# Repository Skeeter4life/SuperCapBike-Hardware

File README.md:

# This repository contains all the hardware needed for my supercapacitor bike.

## Main Features

  A 2 x ((500F @ 2.7V) x 6)  super-capacitor bank-based accumulator:
  
      1. Ability to provide high amounts of current instantaneously.
      
        This is well suited for my application where immediate throttle response is required. 
        The instant delivery of torque allows for aggressive accelerations when 
        changing from a low throttle position to full throttle.  

      2. Much more durable than a traditional battery.
        
        The super-capacitors can withstand many more full charge and discharge cycles
        without degradation. As such, they will undergo many charging cycles through 
        sources such as regenerative braking. Long service life is a priority.
      
      3. Quick charge times.

        Since super-capacitors have significantly less charge density than a battery, 
        it results in faster charging times. The primary intent is to only discharge 
        the super-capacitors to assist in climbing a hill.

  Series-Parallel Switching:

    This allows for a much more dynamic control over the power delivery from the super-capacitors. 
    To maximize runtime, the capacitors can be placed in parallel. 
    When the capacitors are getting low, or a large amount of power is required, 
    they can be switched into series. 

  More specific details can be found [here](https://www.desmos.com/calculator/0xlkaikos0).
    
## Current Components List

Ceramic Capacitors: 
- 0.1uF x 7 [^1], 
- 0.33uF x 2 [^2],
- 1uF x 3 [^3]

Electrolytic capacitors: 
- 10uF x 4 [^4]
  
Diodes:
- 1N4148 x 3 [^5], 
- 1N5819 x 5 [^6]

LEDs: 
- 5.0mm THT x2 [^7]

Fuse: 
- 0225002.MXP x1 [^8], 
- F4658-ND x 1 [^9]

Sockets & Pins: 
- 1x01 1.00mm Vertical Male Pin x 5 [^10], 
- 8 Dip 7.62mm Socket x 5 [^11],
- 16 Dip 7.62mm Socket x 1 [^12], 
- 28 Dip 7.62mm Socket x2 [^13] 

Barrel Jack: 
- PJ_002AH x 1 [^14]

Relays: 
- AWHSH105D00G x 2 [^15]

MOSFETS:
- IRFZ44N x 7 [^16], 
- GT065P06T x 1 [^17]

Resistors: 
- 0Ω, 10Ω, 220Ω, 10kΩ, 22kΩ Resistor Kit: [^18] (Not included in total price!)

Terminals: 
- 1988804 x 1 [^19], 
- 1988817 x 2 [^20], 
- 1190363 x2  [^21], 
- 1988862 x 3 [^22]

Microprocessors: 
- ATMEGA328P x 1 [^23]

Crystal Oscillator: 
- MXO45HST-3C-16M000000 x 1 [^24]

GPIO Expander: 
- MCP23017 x 1 [^25]

Button: 
- TS02-66-50-BK-160-LCR-D x 1 [^26]

MOSFET Gate Driver: 
- UCC37324P x 1 [^27] *OPTIONAL*

Darlington Transistors Array: 
- ULN2003 x 1 [^28]

Digital Potentiometers: 
- MCP4151 x 1 [^29]

Half Bridge Drivers: 
- IR2104 x 3 [^30]

Linear Regulators: 
- L7805 x1 [^31], 
- L78L33ACZ x1 [^32] (Considering upgrading to one that can output more current, I have not decided on display yet, but I had it)

Hall Effect Sensors: 
- TMAG5213AGQLPG x 3 [^33]

Switches: 
- 2057-SW-R-K1-A-ND x 1 [^34] 

Subtotal: **$ 98.21 CAD**

## Schematic and PCB

### Schematic:  

  To reduce image congestion, please clone the repository and access the schematic on Kicad V8+.

### PCB:

<div align="center">

</div>

## FAQ

  -Q: Why are you using only through-hole components?
  
  -A: Since some of these components are new to me, I wanted to be able to quickly set up and re-arrange components on a breadboard so I can fiddle and experiment with them.

  -Q: Why did you choose to design your PCB only with 2 layers?
  
  -A: As the current PCB is only a prototype, I did my best to mitigate EMI, however, I was not too overly concerned with it. I am considering isolating analog and digital ground. My main focus is to test my circuit design on a 2-layer 1oz copper pour PCB and see if any issues need addressing before proceeding to designing a more expensive 2oz copper 4-layer PCB.

  -Q: Why are you using a dedicated MOSFET driver IC to control Q8?
  
  -A: Admittedly, this component is completely optional and absolutely can be replaced with a simple current limiting resistor. Naturally, this does affect the switching speed of the transistor, and I want to maximize performance. I have the IC in hand, and the favourable transient response led me to implement it into my circuit.

  -Q: Why the relays?
  
  -A: I was able to simulate and build a circuit that switches two capacitors in series or parallel with only MOSFETS, however the performance when V_GS < ~4V was inadequate. Additionally, diodes were required to prevent reverse currents from connecting C2- to GND. As such, relays had significantly greater performance when switching the super-capacitors into parallel. I still kept Q7 and Q8 to switch the capacitors into series as a tribute to what I have learned from my experience with MOSFETs.

  -Q: Why did you choose the IRFZ44N?
  
  -A: The IRFZ44N is a widely used, affordable n-type MOSFET, as of which I have many on hand. I am well within the limitations of the drain current I_D, and drain source voltage V_DS. It has a favourable characteristic of only needing a V_GS of ~5.5V to supply 10A at a V_DS of ~ 0.3V. All transients were more than acceptable with the chosen MOSFET drivers for my         application.  

  -Q: Why did you choose the GT065P06T?
  
  -A: I chose the GT065P06T primarily due to its outstanding R_DS of < 11mΩ at V_GS -4.5V for a p-type MOSFET and low gate charge. When the capacitors are in series, I want to minimize the power dissipated through that MOSFET without using PWM. 

## What I am Working on Now

I am currently installing the Hall effect sensors into the motor. The previous sensors were faulty and only outputted an average analog voltage of +3mV. An attempt was made to filter the signal from significant noise with the use of Schmitt triggers, however, this added significantly more complexity and cost. A replacement of the sensors was deemed to be the optimal solution.

## Personal Note

Somehow I managed to get sick twice throughout the last two months! I am doing my best to balance schoolwork and look over my design. I hope to have the PCB ordered by the end of October.

PCB ORDERED! :O

## Sources

[^1]: https://www.digikey.ca/en/products/detail/kemet/C322C104M5U5TA/818107
[^2]: https://www.digikey.ca/en/products/detail/kemet/C330C334M5R5TA/6562403
[^3]: https://www.digikey.ca/en/products/detail/kemet/C330C105K5R5TA7301/3726162
[^4]: https://www.digikey.ca/en/products/detail/cornell-dubilier-knowles/106CKE400M/5410625
[^5]: https://www.digikey.ca/en/products/detail/onsemi/1N4148/458603
[^6]: https://www.digikey.ca/en/products/detail/stmicroelectronics/1N5819/1037326
[^7]: https://www.digikey.ca/en/products/detail/marktech-optoelectronics/MT4118-HR-A/4214622
[^8]: https://www.digikey.ca/en/products/detail/littelfuse-inc/02540101Z/553102
[^9]: https://www.digikey.ca/en/products/detail/littelfuse-inc/0225002-MXP/777781
[^10]: https://www.digikey.ca/en/products/detail/samtec-inc/TS-101-T-A/1105493
[^11]: https://www.digikey.ca/en/products/detail/te-connectivity-amp-connectors/1-2199298-2/5022039
[^12]: https://www.digikey.ca/en/products/detail/on-shore-technology-inc/ED16DT/4147596
[^13]: https://www.digikey.ca/en/products/detail/adam-tech/ICS-328-T/9832859
[^14]: https://www.digikey.ca/en/products/detail/same-sky/PJ-002AH/408446
[^15]: https://www.digikey.ca/en/products/detail/amphenol-anytek/AWHSH105D00G/16721986
[^16]: https://www.digikey.ca/en/products/detail/umw/IRFZ44N/24889964
[^17]: https://www.digikey.ca/en/products/detail/goford-semiconductor/GT065P06T/18088004
[^18]: https://www.digikey.ca/en/products/detail/sparkfun-electronics/COM-10969/14671649
[^19]: https://www.digikey.ca/en/products/detail/phoenix-contact/1988804/950892
[^20]: https://www.digikey.ca/en/products/detail/phoenix-contact/1988817/950893
[^21]: https://www.digikey.ca/en/products/detail/phoenix-contact/1190363/14680902
[^22]: https://www.digikey.ca/en/products/detail/phoenix-contact/1988862/950898
[^23]: https://www.digikey.ca/en/products/detail/microchip-technology/ATMEGA328P-PN/2357094
[^24]: https://www.digikey.ca/en/products/detail/cts-frequency-controls/MXO45HST-3C-16M000000/1801910
[^25]: https://www.digikey.ca/en/products/detail/microchip-technology/MCP23017-E-SP/894272
[^26]: https://www.digikey.ca/en/products/detail/same-sky-formerly-cui-devices/TS02-66-50-BK-160-LCR-D/15634352?s=N4IgTCBcDaICoGUAMYC0A2dqCsTUCEBpVARnTwBkBhAJVQBEACEAXQF8g
[^27]: https://www.digikey.ca/en/products/detail/texas-instruments/UCC37324P/571464
[^28]: https://www.digikey.ca/en/products/detail/stmicroelectronics/ULN2003A/599603
[^29]: https://www.digikey.ca/en/products/detail/microchip-technology/MCP4151-103E-P/1874217
[^30]: https://www.digikey.ca/en/products/detail/infineon-technologies/IR2104PBF/812198
[^31]: https://www.digikey.ca/en/products/detail/stmicroelectronics/L7805CV/585964
[^32]: https://www.digikey.ca/en/products/detail/stmicroelectronics/L78L33ACZ/1038304
[^33]: https://www.digikey.ca/en/products/detail/texas-instruments/TMAG5213AGQLPG/22531584
[^34]: https://www.digikey.ca/en/products/detail/adam-tech/SW-R-K1-A/15284469

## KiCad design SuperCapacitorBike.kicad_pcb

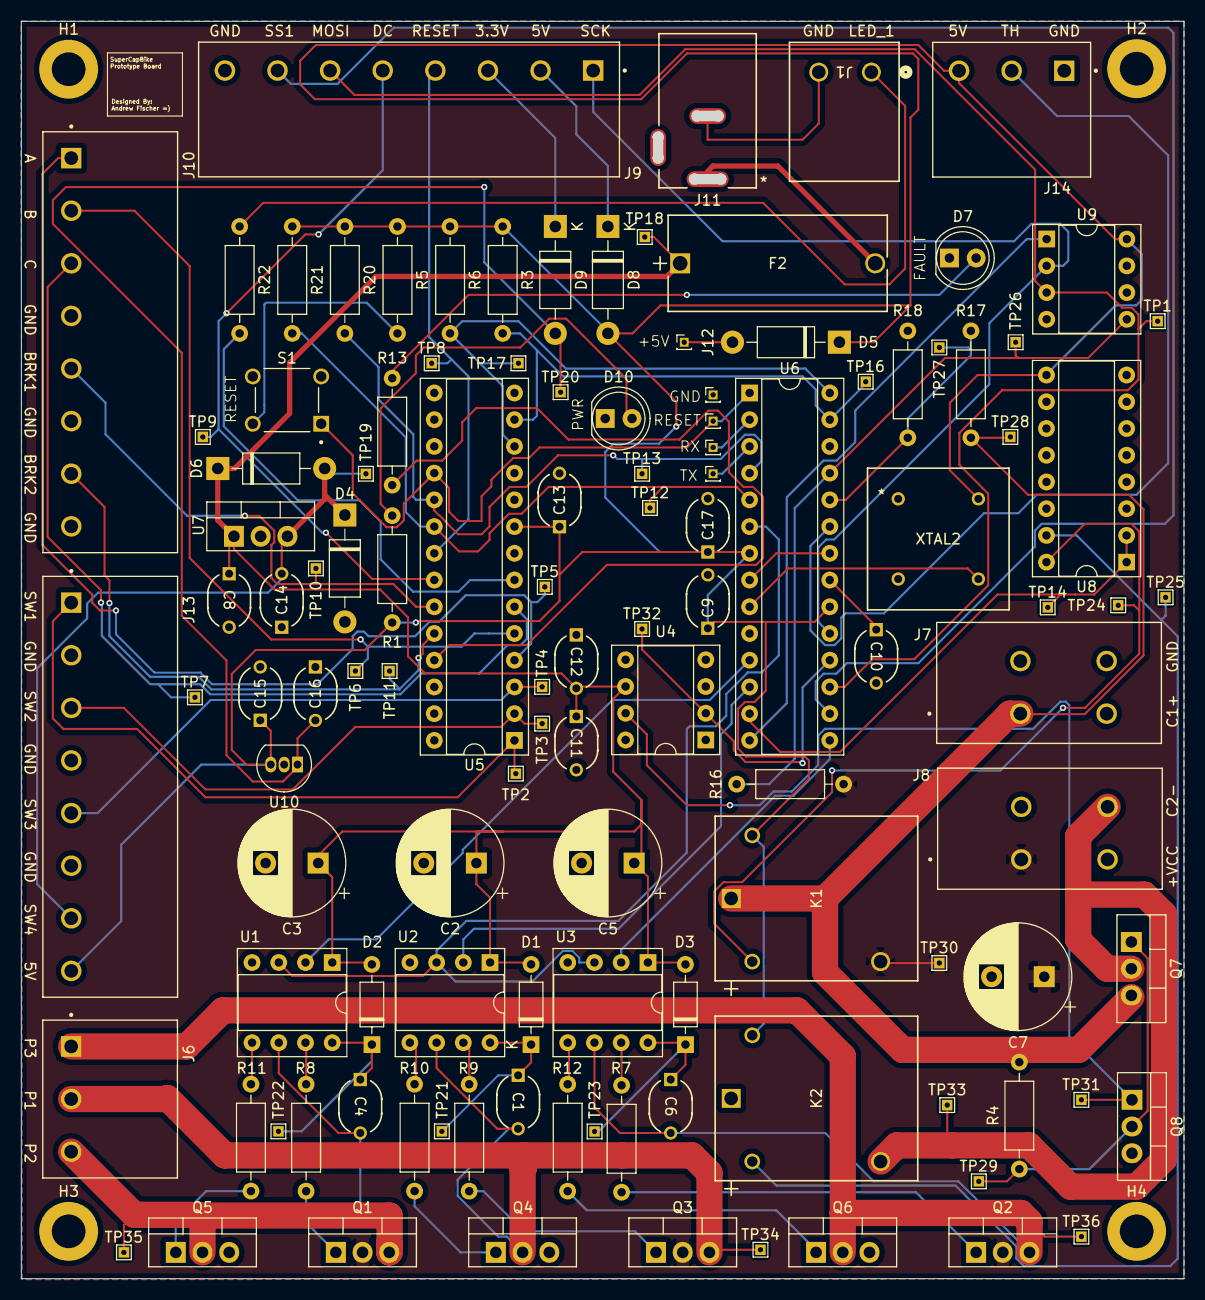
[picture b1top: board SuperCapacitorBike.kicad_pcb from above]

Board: 2 copper layers, 110.5 x 119.5 mm, 121 parts (0 on the bottom side), 71 nets.

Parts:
C1, C4, C6: 1uF; Ceramic_Cap_5.08mm_Spacing
C2, C3, C5, C7: 10uF; CP_Radial_D10.0mm_P5.00mm
C8, C15: 0.33uF; Ceramic_Cap_5.08mm_Spacing
C9, C10, C11, C13, C14, C16, C17: 0.1uF; Ceramic_Cap_5.08mm_Spacing
C12: 1.0uF; Ceramic_Cap_5.08mm_Spacing
D1, D2, D3: 1N4148; D_DO-35_SOD27_P7.62mm_Horizontal
D4, D5, D6, D8, D9: 1N5819; D_DO-41_SOD81_P10.16mm_Horizontal
D7: FAULT_LED; LED_D5.0mm
D10: PWR_LED; LED_D5.0mm
F2: 0225002.MXP; FUSE_254_PC_LTF
H1, H2, H3, H4: MountingHole_Pad; MountingHole_3.2mm_M3_DIN965_Pad
J1: 1988804; CONN_1988804
J2: GND; PinHeader_1x01_P1.00mm_Vertical
J3: RX; PinHeader_1x01_P1.00mm_Vertical
J4: TX; PinHeader_1x01_P1.00mm_Vertical
J5: RESET; PinHeader_1x01_P1.00mm_Vertical
J6, J14: 1988817; PHOENIX_1988817
J7, J8: 1190363; PHOENIX_1190363
J9, J10, J13: 1988862; PHOENIX_1988862
J11: Barrel_Jack_Switch; PJ-002AH_CUD
J12: +5V; PinHeader_1x01_P1.00mm_Vertical
K1, K2: AWHSH105D00G; AWHSH1xxD00G_AMP
Q1, Q2, Q3, Q4, Q5, Q6, Q8: IRFZ44N; TO-220-3_Vertical
Q7: GT065P06T; TO-220-3_Vertical
R1, R13, R22: 220Ω; R_Axial_DIN0207_L6.3mm_D2.5mm_P10.16mm_Horizontal
R3, R4, R5, R6, R20, R21: 10kΩ; R_Axial_DIN0207_L6.3mm_D2.5mm_P10.16mm_Horizontal
R7, R8, R9, R10, R11, R12: 47Ω; R_Axial_DIN0207_L6.3mm_D2.5mm_P10.16mm_Horizontal
R16: 20kΩ; R_Axial_DIN0207_L6.3mm_D2.5mm_P10.16mm_Horizontal
R17: 55kΩ; R_Axial_DIN0207_L6.3mm_D2.5mm_P10.16mm_Horizontal
R18: 25kΩ; R_Axial_DIN0207_L6.3mm_D2.5mm_P10.16mm_Horizontal
S1: TS02-66-50-BK-160-LCR-D; SW_TS02-66-50-BK-160-LCR-D
TP1, TP2, TP3, TP4, TP5, TP6, TP7, TP8, TP9, TP10, TP11, TP12, TP13, TP14, TP16, TP17, TP18, TP19, TP20, TP21, TP22, TP23, TP24, TP25, TP26, TP27, TP28, TP29, TP30, TP31, TP32, TP33, TP34, TP35, TP36: TestPoint; TestPoint_THTPad_1.0x1.0mm_Drill0.5mm
U1, U2, U3: IR2104; DIP-8_W7.62mm_Socket
U4: UCC37324P; DIP-8_W7.62mm_Socket
U5: MCP23017_SP; DIP-28_W7.62mm_Socket
U6: ATmega328-P; DIP-28_W7.62mm_Socket
U7: L7805; TO-220-3_Vertical
U8: ULN2003; DIP-16_W7.62mm_Socket
U9: MCP4151-xxxx-P; DIP-8_W7.62mm_Socket
U10: L78L33_TO92; TO-92_Inline
XTAL2: MXO45HST-3C-16M000000

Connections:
+3.3V: C16.2, D9.2 (A), TP20.1, U10.1 (VO)
+5V: C9.1, C13.1, C15.1, C17.1, D5.1 (K), D8.2 (A), J13.8, J14.3, K1.5, K2.5, R1.1, R3.1, R5.1, R6.1, R20.1, R21.1, U5.9 (VDD), U6.7 (VCC), U6.20 (AVCC), U8.9 (COM), U9.8 (V_{DD}), U10.3 (VI), XTAL2.8 (VCC)
+12V: C2.1, C3.1, C5.1, C8.1, C11.1, C12.2, D1.2 (A), D2.2 (A), D3.2 (A), D6.1 (K), F2.1, F2.2, J11.1, TP18.1, U1.1 (VCC), U2.1 (VCC), U3.1 (VCC), U4.6 (VDD), U7.1 (IN)
+VCC: C7.1, J8.1_1, K1.3, Q1.2 (D), Q2.2 (D), Q3.2 (D), R16.1, TP30.1
/Half bridge Circuit/HO_1: Q3.1 (G), R9.1
/Half bridge Circuit/HO_2: Q1.1 (G), R8.1
/Half bridge Circuit/HO_3: Q2.1 (G), R7.2
/Half bridge Circuit/LO_1: Q4.1 (G), R10.1
/Half bridge Circuit/LO_2: Q5.1 (G), R11.1
/Half bridge Circuit/LO_3: Q6.1 (G), R12.2
/Motor Controller/BRK1: J10.5, TP10.1, U5.23 (GPA2)
/Motor Controller/BRK2: J10.7, TP11.1, U5.24 (GPA3)
/Motor Controller/DC: J9.5, TP9.1, U5.22 (GPA1)
/Motor Controller/HALL_A: J10.1, TP5.1, U5.4 (GPB3)
/Motor Controller/HALL_B: J10.2, TP6.1, U5.5 (GPB4)
/Motor Controller/HALL_C: J10.3, TP7.1, U5.6 (GPB5)
/Motor Controller/INTA: R20.2, TP13.1, U5.19 (INTB), U6.4 (PD2)
/Motor Controller/INTB: R21.2, TP12.1, U5.20 (INTA), U6.5 (PD3)
/Motor Controller/LED_1: J1.1, R22.1
/Motor Controller/RESET: J5.1, S1.1, U5.18 (~RESET), U6.1 (~RESET/PC6)
/Motor Controller/RESET_DISPLAY: J9.4, TP8.1, U5.21 (GPA0)
/Motor Controller/RX: J3.1, U6.2 (PD0)
/Motor Controller/SCL: R6.2, TP17.1, U5.12 (SCK), U6.28 (PC5)
/Motor Controller/SDA: R3.2, TP16.1, U5.13 (SDA), U6.27 (PC4)
/Motor Controller/SW_1: J13.1, TP2.1, U5.1 (GPB0)
/Motor Controller/SW_2: J13.3, TP3.1, U5.2 (GPB1)
/Motor Controller/SW_3: J13.5, TP4.1, U5.3 (GPB2)
/Motor Controller/SW_4: C14.2, D4.1 (K), D6.2 (A), J13.7, TP19.1, U7.3 (OUT)
/Motor Controller/TH_DATA: J14.2, U6.23 (PC0)
/Motor Controller/TX: J4.1, U6.3 (PD1)
/Motor Controller/XTAL1: U6.9 (XTAL1/PB6), XTAL2.5 (OUTPUT)
ADC_C1V: R17.2, R18.1, TP27.1, U6.24 (PC1)
ADC_C2V: R16.2, TP26.1, U6.25 (PC2), U9.5 (P0A)
C1+: J7.1_1, K1.1, Q7.3 (S), R4.1, R17.1, TP28.1
C2-: J8.2_2, K2.3, Q7.2 (D), TP33.1
GND: C2.2, C3.2, C5.2, C7.2, C8.2, C9.2, C10.2, C11.2, C12.1, C13.2, C14.1, C15.2, C16.1, C17.2, D4.2 (A), D7.1 (K), D10.1 (K), H1.1, H2.1, H3.1, H4.1, J1.2, J2.1, J7.2_2, J9.8, J10.4, J10.6, J10.8, J11.2, J13.2, J13.4, J13.6, J14.1, K2.1, Q4.3 (S), Q5.3 (S), Q6.3 (S), Q8.3 (S), R18.2, S1.3, S1.4, U1.4 (COM), U2.4 (COM), U3.4 (COM), U4.3 (GND), U4.4 (INB), U5.10 (VSS), U5.15 (A0), U5.16 (A1), U5.17 (A2), U6.8 (GND), U6.22 (GND), U7.2 (GND), U8.8 (GND), U9.4 (V_{SS}), U9.6 (P0W), U10.2 (GND), XTAL2.4 (GND)
IN_1: U1.2 (IN), U6.12 (PD6)
IN_2: U2.2 (IN), U6.11 (PD5)
IN_3: U3.2 (IN), U6.15 (PB1)
MOSI: J9.6, TP1.1, U6.17 (PB3), U9.3 (SDI/SDO)
MOS_DRIVER: TP32.1, U4.2 (INA), U6.18 (PB4)
unnamed: C1.1, D1.1 (K), TP21.1, U1.8 (VB)
unnamed: C4.1, D2.1 (K), TP22.1, U2.8 (VB)
unnamed: C6.1, D3.1 (K), TP23.1, U3.8 (VB)
unnamed: D5.2 (A), J12.1
unnamed: D7.2 (A), R13.2
unnamed: D8.1 (K), J9.2
unnamed: D9.1 (K), J9.3
unnamed: D10.2 (A), R1.2
unnamed: Q7.1 (G), Q8.2 (D), R4.2, TP29.1
unnamed: Q8.1 (G), TP31.1, U4.7 (OUTA)
unnamed: R5.2, S1.2
unnamed: R9.2, U1.7 (HO)
unnamed: R10.2, U1.5 (LO)
unnamed: R8.2, U2.7 (HO)
unnamed: R11.2, U2.5 (LO)
unnamed: R7.1, U3.7 (HO)
unnamed: R12.1, U3.5 (LO)
unnamed: R13.1, U5.25 (GPA4)
unnamed: R22.2, U5.7 (GPB6)
unnamed: C10.1, U6.21 (AREF)
P1: C1.2, J6.2, Q3.3 (S), Q4.2 (D), TP34.1, U1.6 (VS)
P2: C4.2, J6.3, Q1.3 (S), Q5.2 (D), TP35.1, U2.6 (VS)
P3: C6.2, J6.1, Q2.3 (S), Q6.2 (D), TP36.1, U3.6 (VS)
RELAYS: TP14.1, U6.13 (PD7), U8.1 (I1), U8.2 (I2)
RELAY_1: K1.2, TP24.1, U8.16 (O1)
RELAY_2: K2.2, TP25.1, U8.15 (O2)
SCK: J9.1, U6.19 (PB5), U9.2 (SCK)
SD: U1.3 (~SD), U2.3 (~SD), U3.3 (~SD), U6.6 (PD4)
SS1: J9.7, U6.16 (PB2)
SS2: U6.14 (PB0), U9.1 (~CS)

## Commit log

2024-07-03 Version 1
2024-07-07 Improved filtering & Relay logic
2024-07-12 Added circuit sim. file
2024-09-18 Complete redesign of the schematic
2024-09-28 Made progress on the PCB, and adressed small issues regarding the schematic
2024-10-03 Major design improvements to prototyping PCB
2024-10-07 Create LICENSE
2024-10-08 Rebased 11 commits, Updated README, removed redundent sim file
    Added image files via upload
    For README
    Update README.md
    Update README.md
    Update README.md
    Update README.md
2024-10-08 Added git ignore file
2024-10-08 Added Technical Challenges to README.md
2024-10-17 Removed a couple redundent VIA's, added +5Vpin
2024-10-26 Fixed minor inconsistencies, improved orginization, MOSFET gate resistors calculted.
2024-10-28 Removed alot of redundent VIAs, added testpoints, cleaned up some traces
2024-10-28 Updated all relevent files for repo
2024-10-28 Updated images and gerber file
2024-10-28 Fixed I2C error
2024-10-28 Reviewed gate resistors and removed MOSFET driver resistor
2024-11-03 Prototyping PCB Ordered!
2024-11-12 Updated README to reflect new price and components
2024-11-12 Changed voltage divider resistors
